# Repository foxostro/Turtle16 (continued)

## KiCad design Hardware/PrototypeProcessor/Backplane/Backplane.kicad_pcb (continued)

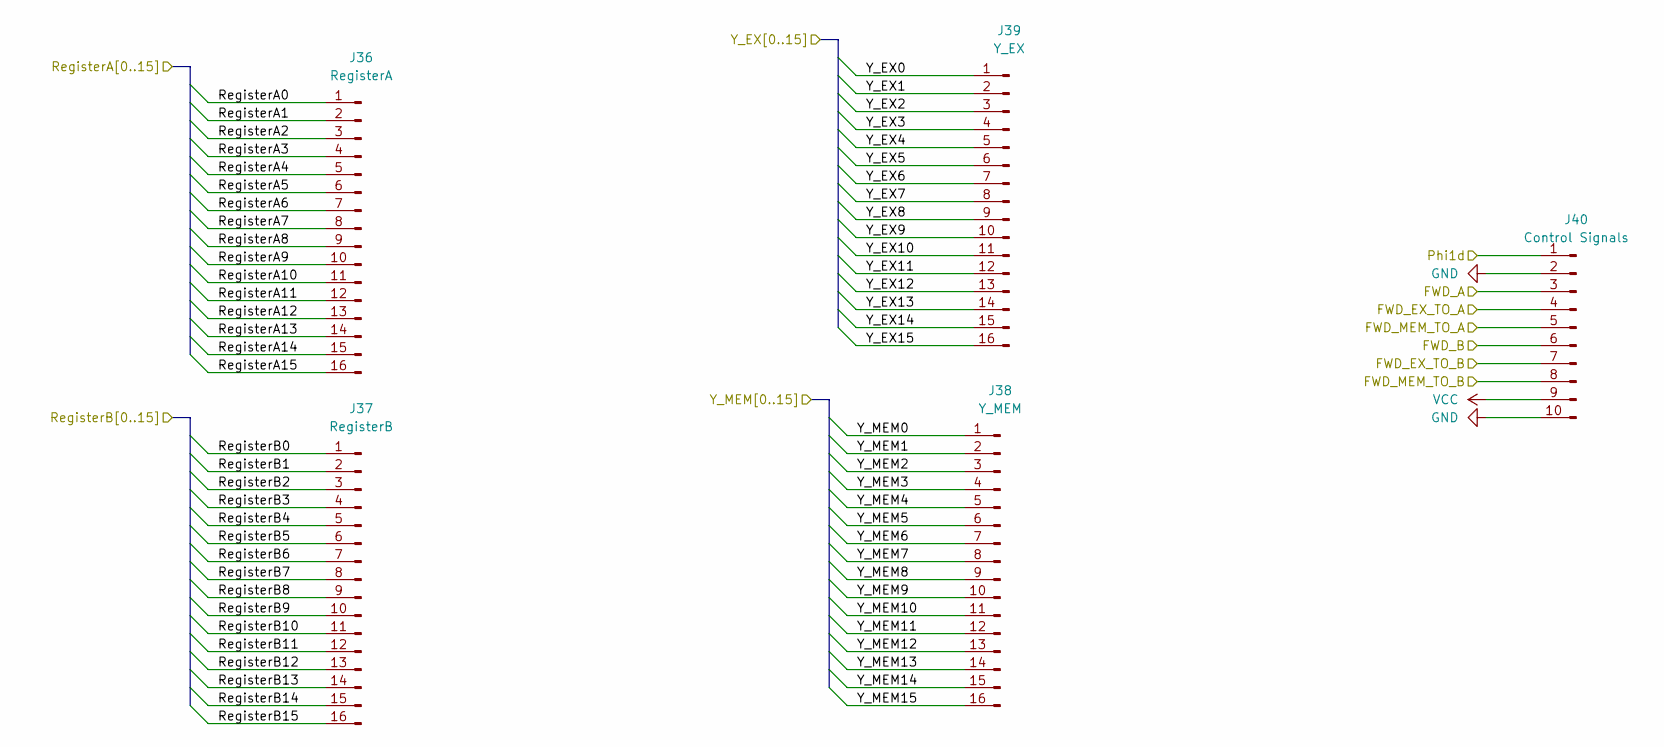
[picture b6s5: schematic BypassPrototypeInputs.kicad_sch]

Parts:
J36: RegisterA; PinHeader_1x16_P2.54mm_Vertical
J37: RegisterB; PinHeader_1x16_P2.54mm_Vertical
J38: Y_MEM; PinHeader_1x16_P2.54mm_Vertical
J39: Y_EX; PinHeader_1x16_P2.54mm_Vertical
J40: Control Signals; PinHeader_1x10_P2.54mm_Vertical

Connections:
/FWD_A: J40.3; also elsewhere on the board
/FWD_B: J40.6; also elsewhere on the board
/FWD_EX_TO_A: J40.4; also elsewhere on the board
/FWD_EX_TO_B: J40.7; also elsewhere on the board
/FWD_MEM_TO_A: J40.5; also elsewhere on the board
/FWD_MEM_TO_B: J40.8; also elsewhere on the board
/Phi1d: J40.1; also elsewhere on the board
/RegisterA0: J36.1; also elsewhere on the board
/RegisterA1: J36.2; also elsewhere on the board
/RegisterA2: J36.3; also elsewhere on the board
/RegisterA3: J36.4; also elsewhere on the board
/RegisterA4: J36.5; also elsewhere on the board
/RegisterA5: J36.6; also elsewhere on the board
/RegisterA6: J36.7; also elsewhere on the board
/RegisterA7: J36.8; also elsewhere on the board
/RegisterA8: J36.9; also elsewhere on the board
/RegisterA9: J36.10; also elsewhere on the board
/RegisterA10: J36.11; also elsewhere on the board
/RegisterA11: J36.12; also elsewhere on the board
/RegisterA12: J36.13; also elsewhere on the board
/RegisterA13: J36.14; also elsewhere on the board
/RegisterA14: J36.15; also elsewhere on the board
/RegisterA15: J36.16; also elsewhere on the board
/RegisterB0: J37.1; also elsewhere on the board
/RegisterB1: J37.2; also elsewhere on the board
/RegisterB2: J37.3; also elsewhere on the board
/RegisterB3: J37.4; also elsewhere on the board
/RegisterB4: J37.5; also elsewhere on the board
/RegisterB5: J37.6; also elsewhere on the board
/RegisterB6: J37.7; also elsewhere on the board
/RegisterB7: J37.8; also elsewhere on the board
/RegisterB8: J37.9; also elsewhere on the board
/RegisterB9: J37.10; also elsewhere on the board
/RegisterB10: J37.11; also elsewhere on the board
/RegisterB11: J37.12; also elsewhere on the board
/RegisterB12: J37.13; also elsewhere on the board
/RegisterB13: J37.14; also elsewhere on the board
/RegisterB14: J37.15; also elsewhere on the board
/RegisterB15: J37.16; also elsewhere on the board
/Y_EX0: J39.1; also elsewhere on the board
/Y_EX1: J39.2; also elsewhere on the board
/Y_EX2: J39.3; also elsewhere on the board
/Y_EX3: J39.4; also elsewhere on the board
/Y_EX4: J39.5; also elsewhere on the board
/Y_EX5: J39.6; also elsewhere on the board
/Y_EX6: J39.7; also elsewhere on the board
/Y_EX7: J39.8; also elsewhere on the board
/Y_EX8: J39.9; also elsewhere on the board
/Y_EX9: J39.10; also elsewhere on the board
/Y_EX10: J39.11; also elsewhere on the board
/Y_EX11: J39.12; also elsewhere on the board
/Y_EX12: J39.13; also elsewhere on the board
/Y_EX13: J39.14; also elsewhere on the board
/Y_EX14: J39.15; also elsewhere on the board
/Y_EX15: J39.16; also elsewhere on the board
/Y_MEM0: J38.1; also elsewhere on the board
/Y_MEM1: J38.2; also elsewhere on the board
/Y_MEM2: J38.3; also elsewhere on the board
/Y_MEM3: J38.4; also elsewhere on the board
/Y_MEM4: J38.5; also elsewhere on the board
/Y_MEM5: J38.6; also elsewhere on the board
/Y_MEM6: J38.7; also elsewhere on the board
/Y_MEM7: J38.8; also elsewhere on the board
/Y_MEM8: J38.9; also elsewhere on the board
/Y_MEM9: J38.10; also elsewhere on the board
/Y_MEM10: J38.11; also elsewhere on the board
/Y_MEM11: J38.12; also elsewhere on the board
/Y_MEM12: J38.13; also elsewhere on the board
/Y_MEM13: J38.14; also elsewhere on the board
/Y_MEM14: J38.15; also elsewhere on the board
/Y_MEM15: J38.16; also elsewhere on the board
GND: J40.2, J40.10; also elsewhere on the board
VCC: J40.9; also elsewhere on the board

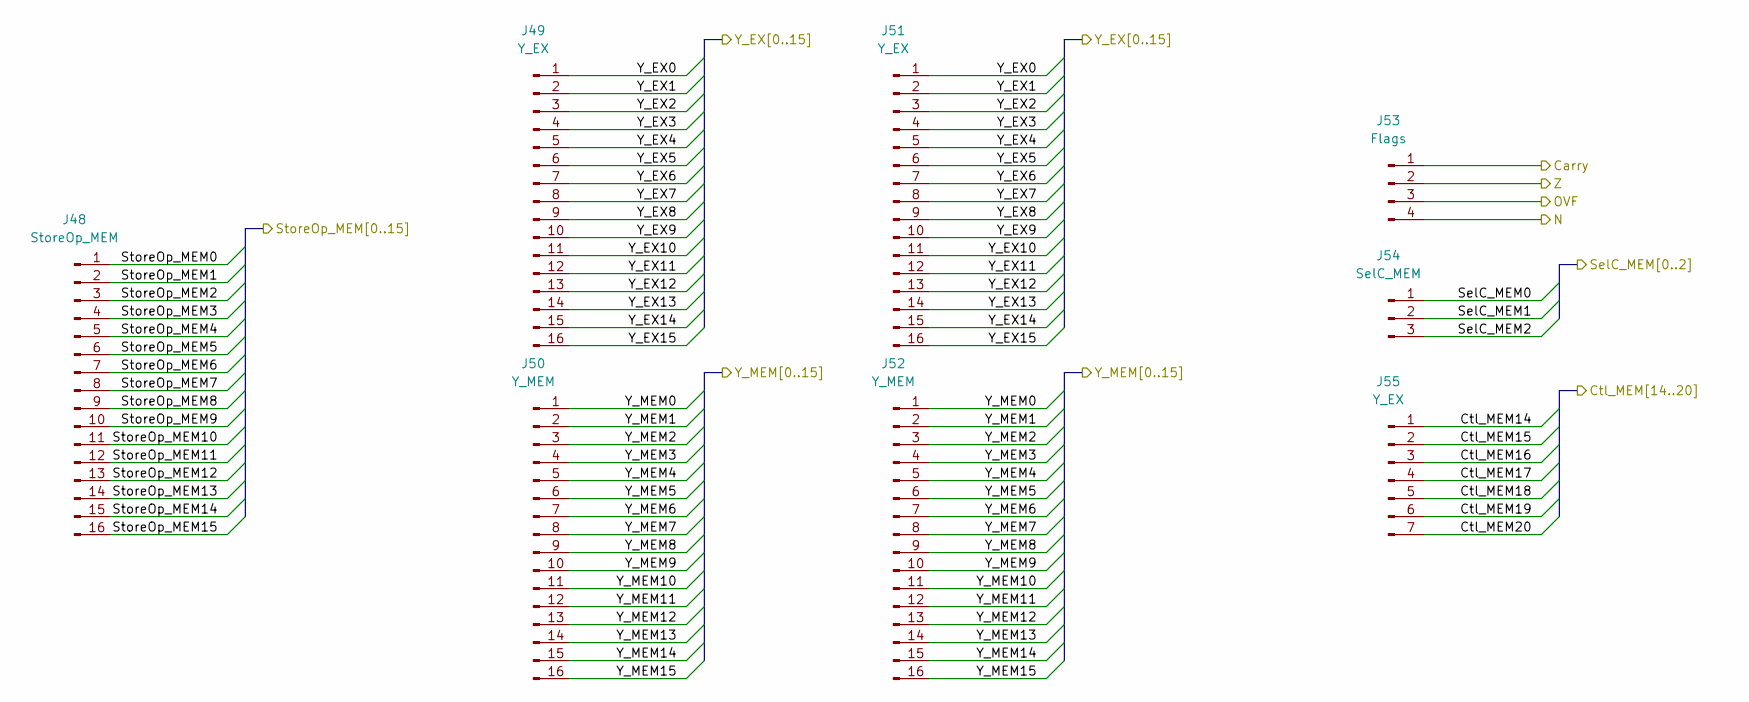
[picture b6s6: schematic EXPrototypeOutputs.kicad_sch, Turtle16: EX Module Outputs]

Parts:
J48: StoreOp_MEM; PinHeader_1x16_P2.54mm_Vertical
J49, J51: Y_EX; PinHeader_1x16_P2.54mm_Vertical
J50, J52: Y_MEM; PinHeader_1x16_P2.54mm_Vertical
J53: Flags; PinHeader_1x04_P2.54mm_Vertical
J54: SelC_MEM; PinHeader_1x03_P2.54mm_Vertical
J55: Y_EX; PinHeader_1x07_P2.54mm_Vertical

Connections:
/Carry: J53.1; also elsewhere on the board
/Ctl_MEM14: J55.1; also elsewhere on the board
/Ctl_MEM15: J55.2; also elsewhere on the board
/Ctl_MEM16: J55.3; also elsewhere on the board
/Ctl_MEM17: J55.4; also elsewhere on the board
/Ctl_MEM18: J55.5; also elsewhere on the board
/Ctl_MEM19: J55.6; also elsewhere on the board
/Ctl_MEM20: J55.7; also elsewhere on the board
/N: J53.4; also elsewhere on the board
/OVF: J53.3; also elsewhere on the board
/SelC_MEM0: J54.1; also elsewhere on the board
/SelC_MEM1: J54.2; also elsewhere on the board
/SelC_MEM2: J54.3; also elsewhere on the board
/StoreOp_MEM0: J48.1; also elsewhere on the board
/StoreOp_MEM1: J48.2; also elsewhere on the board
/StoreOp_MEM2: J48.3; also elsewhere on the board
/StoreOp_MEM3: J48.4; also elsewhere on the board
/StoreOp_MEM4: J48.5; also elsewhere on the board
/StoreOp_MEM5: J48.6; also elsewhere on the board
/StoreOp_MEM6: J48.7; also elsewhere on the board
/StoreOp_MEM7: J48.8; also elsewhere on the board
/StoreOp_MEM8: J48.9; also elsewhere on the board
/StoreOp_MEM9: J48.10; also elsewhere on the board
/StoreOp_MEM10: J48.11; also elsewhere on the board
/StoreOp_MEM11: J48.12; also elsewhere on the board
/StoreOp_MEM12: J48.13; also elsewhere on the board
/StoreOp_MEM13: J48.14; also elsewhere on the board
/StoreOp_MEM14: J48.15; also elsewhere on the board
/StoreOp_MEM15: J48.16; also elsewhere on the board
/Y_EX0: J49.1, J51.1; also elsewhere on the board
/Y_EX1: J49.2, J51.2; also elsewhere on the board
/Y_EX2: J49.3, J51.3; also elsewhere on the board
/Y_EX3: J49.4, J51.4; also elsewhere on the board
/Y_EX4: J49.5, J51.5; also elsewhere on the board
/Y_EX5: J49.6, J51.6; also elsewhere on the board
/Y_EX6: J49.7, J51.7; also elsewhere on the board
/Y_EX7: J49.8, J51.8; also elsewhere on the board
/Y_EX8: J49.9, J51.9; also elsewhere on the board
/Y_EX9: J49.10, J51.10; also elsewhere on the board
/Y_EX10: J49.11, J51.11; also elsewhere on the board
/Y_EX11: J49.12, J51.12; also elsewhere on the board
/Y_EX12: J49.13, J51.13; also elsewhere on the board
/Y_EX13: J49.14, J51.14; also elsewhere on the board
/Y_EX14: J49.15, J51.15; also elsewhere on the board
/Y_EX15: J49.16, J51.16; also elsewhere on the board
/Y_MEM0: J50.1, J52.1; also elsewhere on the board
/Y_MEM1: J50.2, J52.2; also elsewhere on the board
/Y_MEM2: J50.3, J52.3; also elsewhere on the board
/Y_MEM3: J50.4, J52.4; also elsewhere on the board
/Y_MEM4: J50.5, J52.5; also elsewhere on the board
/Y_MEM5: J50.6, J52.6; also elsewhere on the board
/Y_MEM6: J50.7, J52.7; also elsewhere on the board
/Y_MEM7: J50.8, J52.8; also elsewhere on the board
/Y_MEM8: J50.9, J52.9; also elsewhere on the board
/Y_MEM9: J50.10, J52.10; also elsewhere on the board
/Y_MEM10: J50.11, J52.11; also elsewhere on the board
/Y_MEM11: J50.12, J52.12; also elsewhere on the board
/Y_MEM12: J50.13, J52.13; also elsewhere on the board
/Y_MEM13: J50.14, J52.14; also elsewhere on the board
/Y_MEM14: J50.15, J52.15; also elsewhere on the board
/Y_MEM15: J50.16, J52.16; also elsewhere on the board
/Z: J53.2; also elsewhere on the board

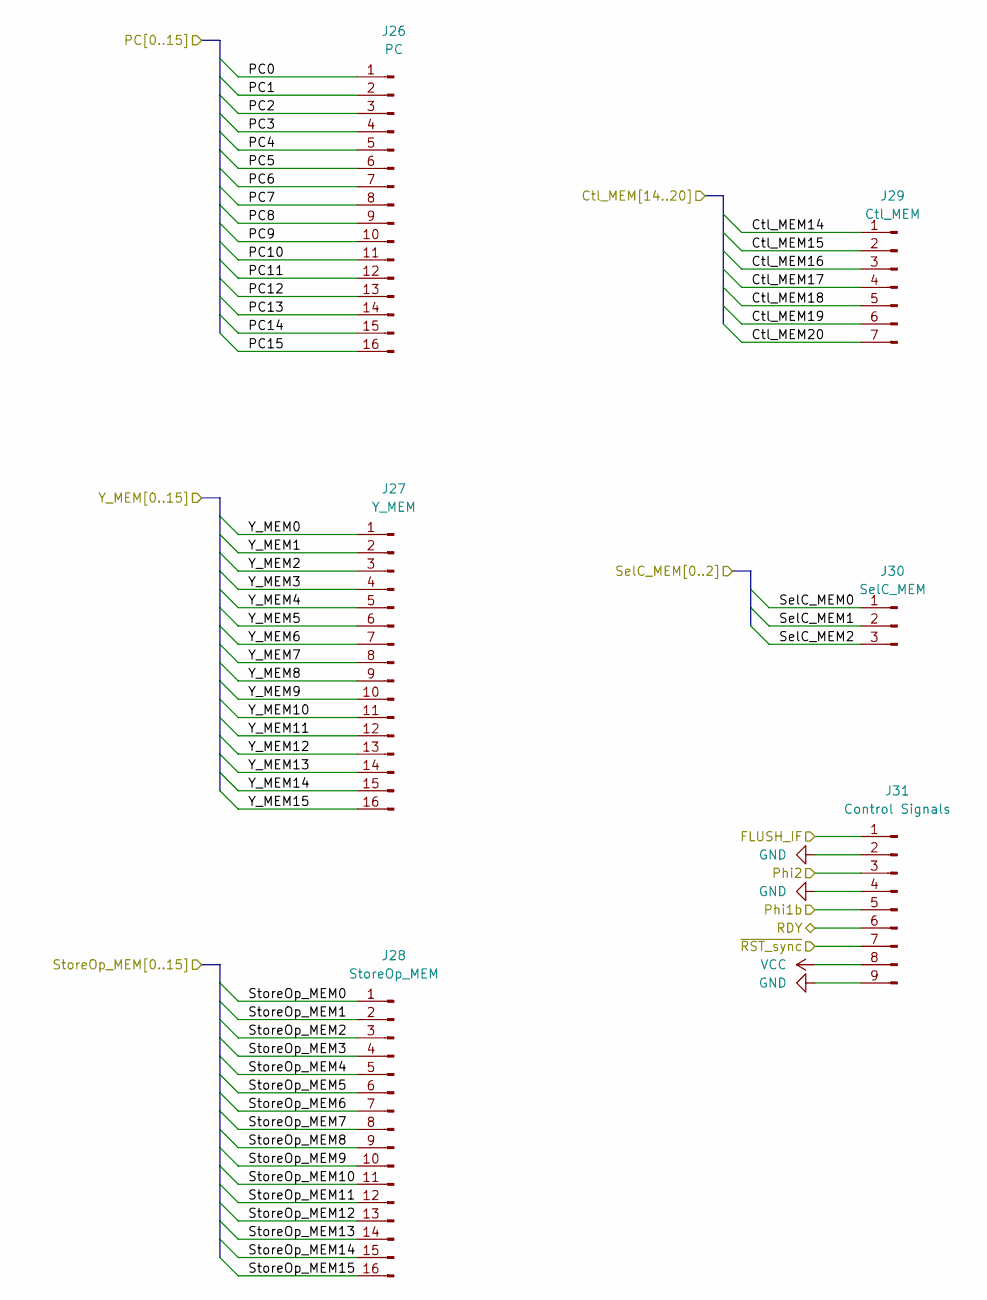
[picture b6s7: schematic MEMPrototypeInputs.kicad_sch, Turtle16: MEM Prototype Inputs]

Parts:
J26: PC; PinHeader_1x16_P2.54mm_Vertical
J27: Y_MEM; PinHeader_1x16_P2.54mm_Vertical
J28: StoreOp_MEM; PinHeader_1x16_P2.54mm_Vertical
J29: Ctl_MEM; PinHeader_1x07_P2.54mm_Vertical
J30: SelC_MEM; PinHeader_1x03_P2.54mm_Vertical
J31: Control Signals; PinHeader_1x09_P2.54mm_Vertical

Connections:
/Ctl_MEM14: J29.1; also elsewhere on the board
/Ctl_MEM15: J29.2; also elsewhere on the board
/Ctl_MEM16: J29.3; also elsewhere on the board
/Ctl_MEM17: J29.4; also elsewhere on the board
/Ctl_MEM18: J29.5; also elsewhere on the board
/Ctl_MEM19: J29.6; also elsewhere on the board
/Ctl_MEM20: J29.7; also elsewhere on the board
/FLUSH_IF: J31.1; also elsewhere on the board
/PC0: J26.1; also elsewhere on the board
/PC1: J26.2; also elsewhere on the board
/PC2: J26.3; also elsewhere on the board
/PC3: J26.4; also elsewhere on the board
/PC4: J26.5; also elsewhere on the board
/PC5: J26.6; also elsewhere on the board
/PC6: J26.7; also elsewhere on the board
/PC7: J26.8; also elsewhere on the board
/PC8: J26.9; also elsewhere on the board
/PC9: J26.10; also elsewhere on the board
/PC10: J26.11; also elsewhere on the board
/PC11: J26.12; also elsewhere on the board
/PC12: J26.13; also elsewhere on the board
/PC13: J26.14; also elsewhere on the board
/PC14: J26.15; also elsewhere on the board
/PC15: J26.16; also elsewhere on the board
/Phi1b: J31.5; also elsewhere on the board
/Phi2: J31.3; also elsewhere on the board
/RDY: J31.6; also elsewhere on the board
/SelC_MEM0: J30.1; also elsewhere on the board
/SelC_MEM1: J30.2; also elsewhere on the board
/SelC_MEM2: J30.3; also elsewhere on the board
/StoreOp_MEM0: J28.1; also elsewhere on the board
/StoreOp_MEM1: J28.2; also elsewhere on the board
/StoreOp_MEM2: J28.3; also elsewhere on the board
/StoreOp_MEM3: J28.4; also elsewhere on the board
/StoreOp_MEM4: J28.5; also elsewhere on the board
/StoreOp_MEM5: J28.6; also elsewhere on the board
/StoreOp_MEM6: J28.7; also elsewhere on the board
/StoreOp_MEM7: J28.8; also elsewhere on the board
/StoreOp_MEM8: J28.9; also elsewhere on the board
/StoreOp_MEM9: J28.10; also elsewhere on the board
/StoreOp_MEM10: J28.11; also elsewhere on the board
/StoreOp_MEM11: J28.12; also elsewhere on the board
/StoreOp_MEM12: J28.13; also elsewhere on the board
/StoreOp_MEM13: J28.14; also elsewhere on the board
/StoreOp_MEM14: J28.15; also elsewhere on the board
/StoreOp_MEM15: J28.16; also elsewhere on the board
/Y_MEM0: J27.1; also elsewhere on the board
/Y_MEM1: J27.2; also elsewhere on the board
/Y_MEM2: J27.3; also elsewhere on the board
/Y_MEM3: J27.4; also elsewhere on the board
/Y_MEM4: J27.5; also elsewhere on the board
/Y_MEM5: J27.6; also elsewhere on the board
/Y_MEM6: J27.7; also elsewhere on the board
/Y_MEM7: J27.8; also elsewhere on the board
/Y_MEM8: J27.9; also elsewhere on the board
/Y_MEM9: J27.10; also elsewhere on the board
/Y_MEM10: J27.11; also elsewhere on the board
/Y_MEM11: J27.12; also elsewhere on the board
/Y_MEM12: J27.13; also elsewhere on the board
/Y_MEM13: J27.14; also elsewhere on the board
/Y_MEM14: J27.15; also elsewhere on the board
/Y_MEM15: J27.16; also elsewhere on the board
/~RST_sync: J31.7; also elsewhere on the board
GND: J31.2, J31.4, J31.9; also elsewhere on the board
VCC: J31.8; also elsewhere on the board

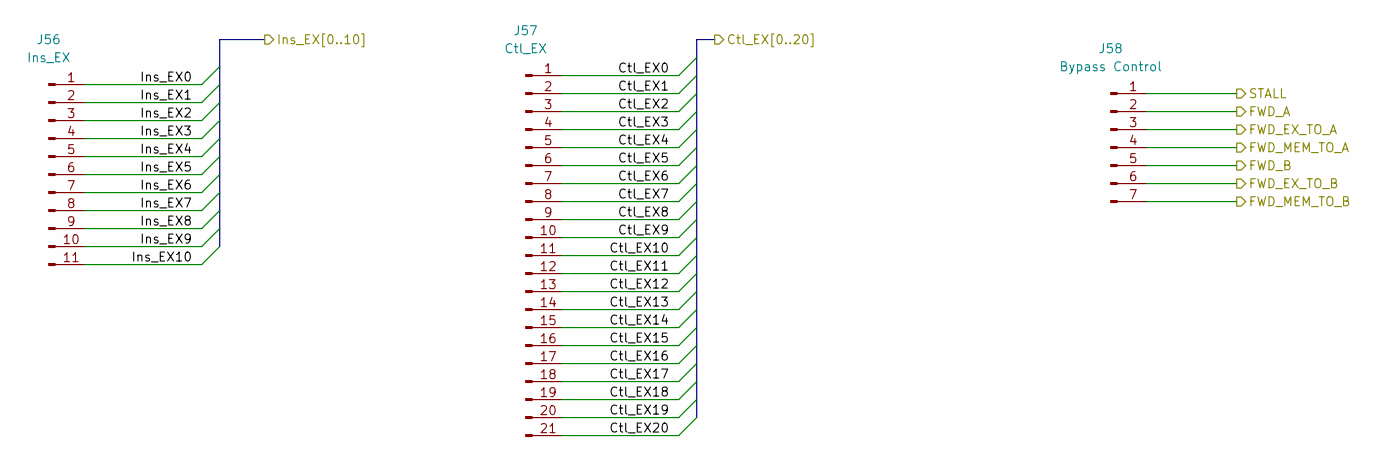
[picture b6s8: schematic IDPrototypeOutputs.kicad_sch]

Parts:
J56: Ins_EX; PinHeader_1x11_P2.54mm_Vertical
J57: Ctl_EX; PinHeader_1x21_P2.54mm_Vertical
J58: Bypass Control; PinHeader_1x07_P2.54mm_Vertical

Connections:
/Ctl_EX0: J57.1; also elsewhere on the board
/Ctl_EX1: J57.2; also elsewhere on the board
/Ctl_EX2: J57.3; also elsewhere on the board
/Ctl_EX3: J57.4; also elsewhere on the board
/Ctl_EX4: J57.5; also elsewhere on the board
/Ctl_EX5: J57.6; also elsewhere on the board
/Ctl_EX6: J57.7; also elsewhere on the board
/Ctl_EX7: J57.8; also elsewhere on the board
/Ctl_EX8: J57.9; also elsewhere on the board
/Ctl_EX9: J57.10; also elsewhere on the board
/Ctl_EX10: J57.11; also elsewhere on the board
/Ctl_EX11: J57.12; also elsewhere on the board
/Ctl_EX12: J57.13; also elsewhere on the board
/Ctl_EX13: J57.14; also elsewhere on the board
/Ctl_EX14: J57.15; also elsewhere on the board
/Ctl_EX15: J57.16; also elsewhere on the board
/Ctl_EX16: J57.17; also elsewhere on the board
/Ctl_EX17: J57.18; also elsewhere on the board
/Ctl_EX18: J57.19; also elsewhere on the board
/Ctl_EX19: J57.20; also elsewhere on the board
/Ctl_EX20: J57.21; also elsewhere on the board
/FWD_A: J58.2; also elsewhere on the board
/FWD_B: J58.5; also elsewhere on the board
/FWD_EX_TO_A: J58.3; also elsewhere on the board
/FWD_EX_TO_B: J58.6; also elsewhere on the board
/FWD_MEM_TO_A: J58.4; also elsewhere on the board
/FWD_MEM_TO_B: J58.7; also elsewhere on the board
/Ins_EX0: J56.1; also elsewhere on the board
/Ins_EX1: J56.2; also elsewhere on the board
/Ins_EX2: J56.3; also elsewhere on the board
/Ins_EX3: J56.4; also elsewhere on the board
/Ins_EX4: J56.5; also elsewhere on the board
/Ins_EX5: J56.6; also elsewhere on the board
/Ins_EX6: J56.7; also elsewhere on the board
/Ins_EX7: J56.8; also elsewhere on the board
/Ins_EX8: J56.9; also elsewhere on the board
/Ins_EX9: J56.10; also elsewhere on the board
/Ins_EX10: J56.11; also elsewhere on the board
/STALL: J58.1; also elsewhere on the board

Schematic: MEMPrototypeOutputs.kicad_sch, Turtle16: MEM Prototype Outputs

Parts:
J43: StoreOp_WB; PinHeader_1x16_P2.54mm_Vertical
J44: Ins_IF; PinHeader_1x16_P2.54mm_Vertical
J45: SelC_MEM; PinHeader_1x03_P2.54mm_Vertical
J46: Y_WB; PinHeader_1x16_P2.54mm_Vertical
J47: Ctl_MEM; PinHeader_1x04_P2.54mm_Vertical

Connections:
/Ctl_WB17: J47.1; also elsewhere on the board
/Ctl_WB18: J47.2; also elsewhere on the board
/Ctl_WB19: J47.3; also elsewhere on the board
/Ctl_WB20: J47.4; also elsewhere on the board
/Ins_IF0: J44.1; also elsewhere on the board
/Ins_IF1: J44.2; also elsewhere on the board
/Ins_IF2: J44.3; also elsewhere on the board
/Ins_IF3: J44.4; also elsewhere on the board
/Ins_IF4: J44.5; also elsewhere on the board
/Ins_IF5: J44.6; also elsewhere on the board
/Ins_IF6: J44.7; also elsewhere on the board
/Ins_IF7: J44.8; also elsewhere on the board
/Ins_IF8: J44.9; also elsewhere on the board
/Ins_IF9: J44.10; also elsewhere on the board
/Ins_IF10: J44.11; also elsewhere on the board
/Ins_IF11: J44.12; also elsewhere on the board
/Ins_IF12: J44.13; also elsewhere on the board
/Ins_IF13: J44.14; also elsewhere on the board
/Ins_IF14: J44.15; also elsewhere on the board
/Ins_IF15: J44.16; also elsewhere on the board
/SelC_WB0: J45.1; also elsewhere on the board
/SelC_WB1: J45.2; also elsewhere on the board
/SelC_WB2: J45.3; also elsewhere on the board
/StoreOp_WB0: J43.1; also elsewhere on the board
/StoreOp_WB1: J43.2; also elsewhere on the board
/StoreOp_WB2: J43.3; also elsewhere on the board
/StoreOp_WB3: J43.4; also elsewhere on the board
/StoreOp_WB4: J43.5; also elsewhere on the board
/StoreOp_WB5: J43.6; also elsewhere on the board
/StoreOp_WB6: J43.7; also elsewhere on the board
/StoreOp_WB7: J43.8; also elsewhere on the board
/StoreOp_WB8: J43.9; also elsewhere on the board
/StoreOp_WB9: J43.10; also elsewhere on the board
/StoreOp_WB10: J43.11; also elsewhere on the board
/StoreOp_WB11: J43.12; also elsewhere on the board
/StoreOp_WB12: J43.13; also elsewhere on the board
/StoreOp_WB13: J43.14; also elsewhere on the board
/StoreOp_WB14: J43.15; also elsewhere on the board
/StoreOp_WB15: J43.16; also elsewhere on the board
/Y_WB0: J46.1; also elsewhere on the board
/Y_WB1: J46.2; also elsewhere on the board
/Y_WB2: J46.3; also elsewhere on the board
/Y_WB3: J46.4; also elsewhere on the board
/Y_WB4: J46.5; also elsewhere on the board
/Y_WB5: J46.6; also elsewhere on the board
/Y_WB6: J46.7; also elsewhere on the board
/Y_WB7: J46.8; also elsewhere on the board
/Y_WB8: J46.9; also elsewhere on the board
/Y_WB9: J46.10; also elsewhere on the board
/Y_WB10: J46.11; also elsewhere on the board
/Y_WB11: J46.12; also elsewhere on the board
/Y_WB12: J46.13; also elsewhere on the board
/Y_WB13: J46.14; also elsewhere on the board
/Y_WB14: J46.15; also elsewhere on the board
/Y_WB15: J46.16; also elsewhere on the board

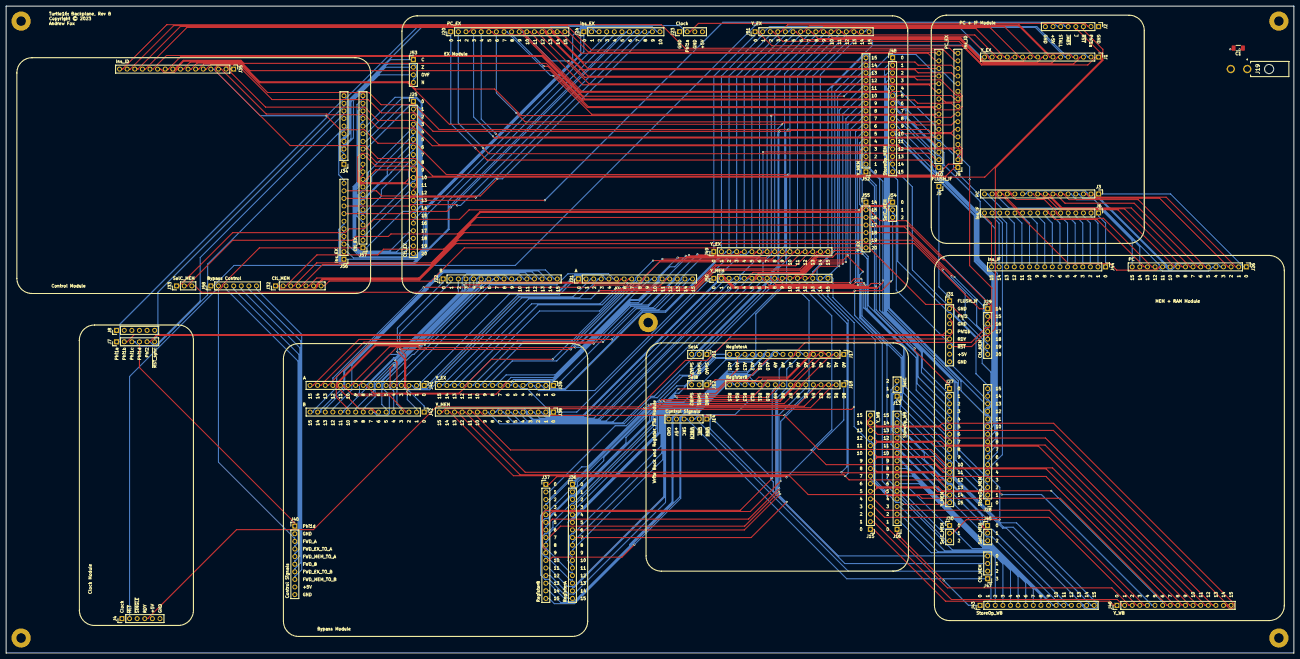
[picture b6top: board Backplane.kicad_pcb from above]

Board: 4 copper layers, 430.0 x 216.0 mm, 64 parts (0 on the bottom side), 278 nets.

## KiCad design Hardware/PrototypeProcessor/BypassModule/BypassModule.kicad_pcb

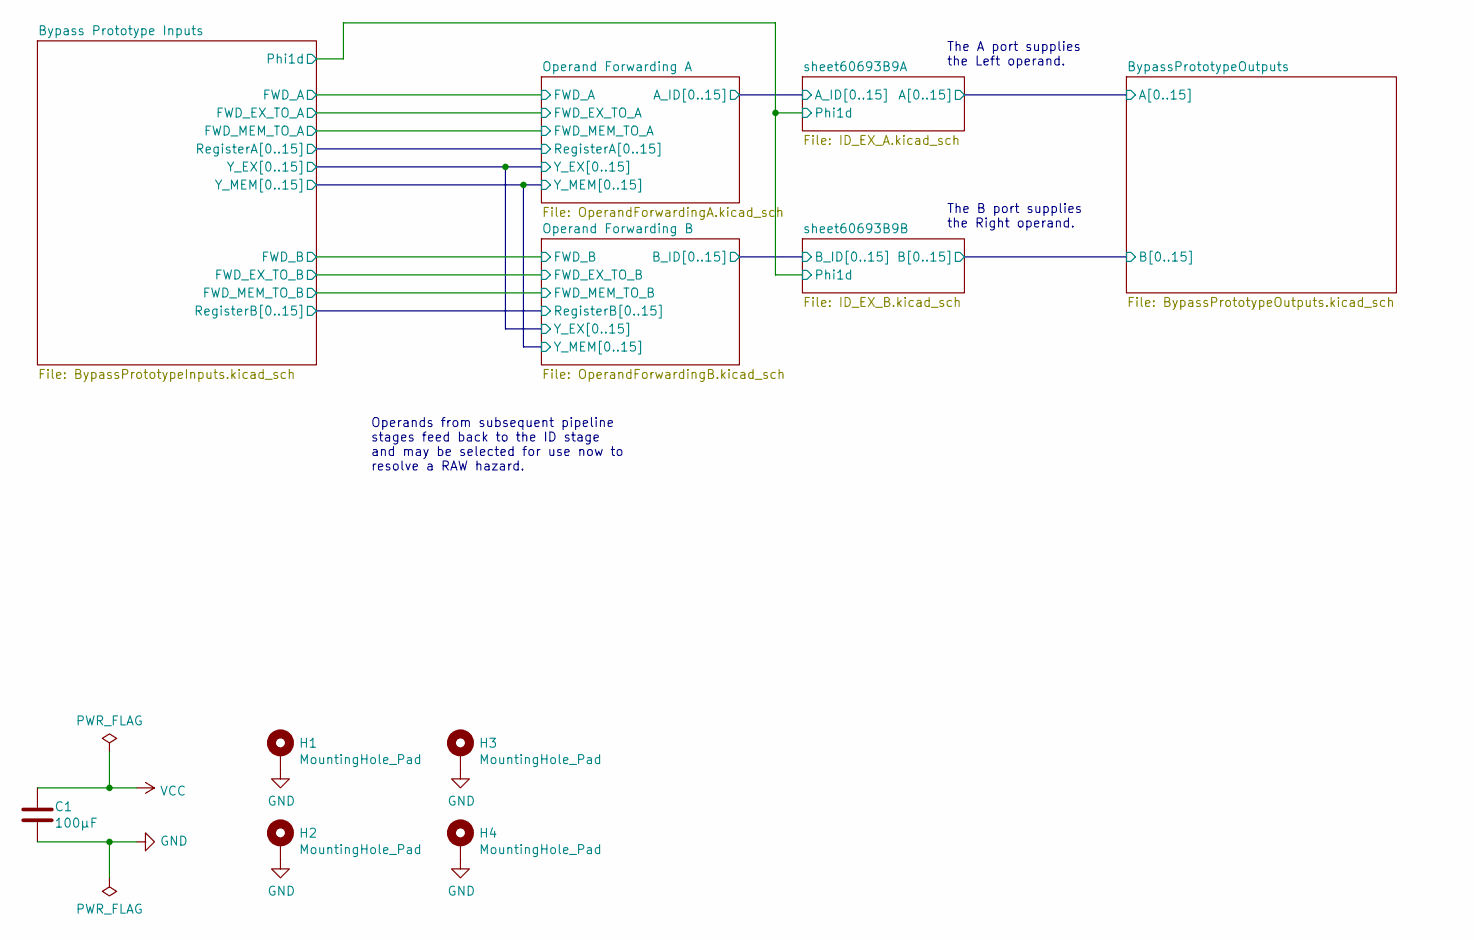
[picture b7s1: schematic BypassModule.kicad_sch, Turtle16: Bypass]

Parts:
C1: 100µF; C_1206_3216Metric_Pad1.33x1.80mm_HandSolder
H1, H2, H3, H4: MountingHole_Pad; MountingHole_3.2mm_M3_Pad

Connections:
GND: C1.2, H1.1, H2.1, H3.1, H4.1; also elsewhere on the board
VCC: C1.1; also elsewhere on the board

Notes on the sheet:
Operands from subsequent pipeline stages feed back to the ID stage and may be selected for use now to resolve a RAW hazard.
The B port supplies the Right operand.
The A port supplies the Left operand.

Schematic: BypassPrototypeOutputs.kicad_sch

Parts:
J6: A; PinHeader_1x16_P2.54mm_Vertical
J7: B; PinHeader_1x16_P2.54mm_Vertical

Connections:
/BypassPrototypeOutputs/A0: J6.1; also elsewhere on the board
/BypassPrototypeOutputs/A1: J6.2; also elsewhere on the board
/BypassPrototypeOutputs/A2: J6.3; also elsewhere on the board
/BypassPrototypeOutputs/A3: J6.4; also elsewhere on the board
/BypassPrototypeOutputs/A4: J6.5; also elsewhere on the board
/BypassPrototypeOutputs/A5: J6.6; also elsewhere on the board
/BypassPrototypeOutputs/A6: J6.7; also elsewhere on the board
/BypassPrototypeOutputs/A7: J6.8; also elsewhere on the board
/BypassPrototypeOutputs/A8: J6.9; also elsewhere on the board
/BypassPrototypeOutputs/A9: J6.10; also elsewhere on the board
/BypassPrototypeOutputs/A10: J6.11; also elsewhere on the board
/BypassPrototypeOutputs/A11: J6.12; also elsewhere on the board
/BypassPrototypeOutputs/A12: J6.13; also elsewhere on the board
/BypassPrototypeOutputs/A13: J6.14; also elsewhere on the board
/BypassPrototypeOutputs/A14: J6.15; also elsewhere on the board
/BypassPrototypeOutputs/A15: J6.16; also elsewhere on the board
/BypassPrototypeOutputs/B0: J7.1; also elsewhere on the board
/BypassPrototypeOutputs/B1: J7.2; also elsewhere on the board
/BypassPrototypeOutputs/B2: J7.3; also elsewhere on the board
/BypassPrototypeOutputs/B3: J7.4; also elsewhere on the board
/BypassPrototypeOutputs/B4: J7.5; also elsewhere on the board
/BypassPrototypeOutputs/B5: J7.6; also elsewhere on the board
/BypassPrototypeOutputs/B6: J7.7; also elsewhere on the board
/BypassPrototypeOutputs/B7: J7.8; also elsewhere on the board
/BypassPrototypeOutputs/B8: J7.9; also elsewhere on the board
/BypassPrototypeOutputs/B9: J7.10; also elsewhere on the board
/BypassPrototypeOutputs/B10: J7.11; also elsewhere on the board
/BypassPrototypeOutputs/B11: J7.12; also elsewhere on the board
/BypassPrototypeOutputs/B12: J7.13; also elsewhere on the board
/BypassPrototypeOutputs/B13: J7.14; also elsewhere on the board
/BypassPrototypeOutputs/B14: J7.15; also elsewhere on the board
/BypassPrototypeOutputs/B15: J7.16; also elsewhere on the board

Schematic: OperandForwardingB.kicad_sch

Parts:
C5, C6, C7: 100nF; C_0603_1608Metric_Pad1.08x0.95mm_HandSolder
U4, U5, U6: 74AHCT16245; TSSOP-48_6.1x12.5mm_P0.5mm

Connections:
/Bypass Prototype Inputs/FWD_B: U4.25 (2~OE), U4.48 (1~OE); also elsewhere on the board
/Bypass Prototype Inputs/FWD_EX_TO_B: U5.25 (2~OE), U5.48 (1~OE); also elsewhere on the board
/Bypass Prototype Inputs/FWD_MEM_TO_B: U6.25 (2~OE), U6.48 (1~OE); also elsewhere on the board
/Bypass Prototype Inputs/RegisterB0: U4.47 (1A1); also elsewhere on the board
/Bypass Prototype Inputs/RegisterB1: U4.46 (1A2); also elsewhere on the board
/Bypass Prototype Inputs/RegisterB2: U4.44 (1A3); also elsewhere on the board
/Bypass Prototype Inputs/RegisterB3: U4.43 (1A4); also elsewhere on the board
/Bypass Prototype Inputs/RegisterB4: U4.41 (1A5); also elsewhere on the board
/Bypass Prototype Inputs/RegisterB5: U4.40 (1A6); also elsewhere on the board
/Bypass Prototype Inputs/RegisterB6: U4.38 (1A7); also elsewhere on the board
/Bypass Prototype Inputs/RegisterB7: U4.37 (1A8); also elsewhere on the board
/Bypass Prototype Inputs/RegisterB8: U4.36 (2A1); also elsewhere on the board
/Bypass Prototype Inputs/RegisterB9: U4.35 (2A2); also elsewhere on the board
/Bypass Prototype Inputs/RegisterB10: U4.33 (2A3); also elsewhere on the board
/Bypass Prototype Inputs/RegisterB11: U4.32 (2A4); also elsewhere on the board
/Bypass Prototype Inputs/RegisterB12: U4.30 (2A5); also elsewhere on the board
/Bypass Prototype Inputs/RegisterB13: U4.29 (2A6); also elsewhere on the board
/Bypass Prototype Inputs/RegisterB14: U4.27 (2A7); also elsewhere on the board
/Bypass Prototype Inputs/RegisterB15: U4.26 (2A8); also elsewhere on the board
/Bypass Prototype Inputs/Y_EX0: U5.47 (1A1); also elsewhere on the board
/Bypass Prototype Inputs/Y_EX1: U5.46 (1A2); also elsewhere on the board
/Bypass Prototype Inputs/Y_EX2: U5.44 (1A3); also elsewhere on the board
/Bypass Prototype Inputs/Y_EX3: U5.43 (1A4); also elsewhere on the board
/Bypass Prototype Inputs/Y_EX4: U5.41 (1A5); also elsewhere on the board
/Bypass Prototype Inputs/Y_EX5: U5.40 (1A6); also elsewhere on the board
/Bypass Prototype Inputs/Y_EX6: U5.38 (1A7); also elsewhere on the board
/Bypass Prototype Inputs/Y_EX7: U5.37 (1A8); also elsewhere on the board
/Bypass Prototype Inputs/Y_EX8: U5.36 (2A1); also elsewhere on the board
/Bypass Prototype Inputs/Y_EX9: U5.35 (2A2); also elsewhere on the board
/Bypass Prototype Inputs/Y_EX10: U5.33 (2A3); also elsewhere on the board
/Bypass Prototype Inputs/Y_EX11: U5.32 (2A4); also elsewhere on the board
/Bypass Prototype Inputs/Y_EX12: U5.30 (2A5); also elsewhere on the board
/Bypass Prototype Inputs/Y_EX13: U5.29 (2A6); also elsewhere on the board
/Bypass Prototype Inputs/Y_EX14: U5.27 (2A7); also elsewhere on the board
/Bypass Prototype Inputs/Y_EX15: U5.26 (2A8); also elsewhere on the board
/Bypass Prototype Inputs/Y_MEM0: U6.47 (1A1); also elsewhere on the board
/Bypass Prototype Inputs/Y_MEM1: U6.46 (1A2); also elsewhere on the board
/Bypass Prototype Inputs/Y_MEM2: U6.44 (1A3); also elsewhere on the board
/Bypass Prototype Inputs/Y_MEM3: U6.43 (1A4); also elsewhere on the board
/Bypass Prototype Inputs/Y_MEM4: U6.41 (1A5); also elsewhere on the board
/Bypass Prototype Inputs/Y_MEM5: U6.40 (1A6); also elsewhere on the board
/Bypass Prototype Inputs/Y_MEM6: U6.38 (1A7); also elsewhere on the board
/Bypass Prototype Inputs/Y_MEM7: U6.37 (1A8); also elsewhere on the board
/Bypass Prototype Inputs/Y_MEM8: U6.36 (2A1); also elsewhere on the board
/Bypass Prototype Inputs/Y_MEM9: U6.35 (2A2); also elsewhere on the board
/Bypass Prototype Inputs/Y_MEM10: U6.33 (2A3); also elsewhere on the board
/Bypass Prototype Inputs/Y_MEM11: U6.32 (2A4); also elsewhere on the board
/Bypass Prototype Inputs/Y_MEM12: U6.30 (2A5); also elsewhere on the board
/Bypass Prototype Inputs/Y_MEM13: U6.29 (2A6); also elsewhere on the board
/Bypass Prototype Inputs/Y_MEM14: U6.27 (2A7); also elsewhere on the board
/Bypass Prototype Inputs/Y_MEM15: U6.26 (2A8); also elsewhere on the board
/Operand Forwarding B/B_ID0: U4.2 (1B1), U5.2 (1B1), U6.2 (1B1); also elsewhere on the board
/Operand Forwarding B/B_ID1: U4.3 (1B2), U5.3 (1B2), U6.3 (1B2); also elsewhere on the board
/Operand Forwarding B/B_ID2: U4.5 (1B3), U5.5 (1B3), U6.5 (1B3); also elsewhere on the board
/Operand Forwarding B/B_ID3: U4.6 (1B4), U5.6 (1B4), U6.6 (1B4); also elsewhere on the board
/Operand Forwarding B/B_ID4: U4.8 (1B5), U5.8 (1B5), U6.8 (1B5); also elsewhere on the board
/Operand Forwarding B/B_ID5: U4.9 (1B6), U5.9 (1B6), U6.9 (1B6); also elsewhere on the board
/Operand Forwarding B/B_ID6: U4.11 (1B7), U5.11 (1B7), U6.11 (1B7); also elsewhere on the board
/Operand Forwarding B/B_ID7: U4.12 (1B8), U5.12 (1B8), U6.12 (1B8); also elsewhere on the board
/Operand Forwarding B/B_ID8: U4.13 (2B1), U5.13 (2B1), U6.13 (2B1); also elsewhere on the board
/Operand Forwarding B/B_ID9: U4.14 (2B2), U5.14 (2B2), U6.14 (2B2); also elsewhere on the board
/Operand Forwarding B/B_ID10: U4.16 (2B3), U5.16 (2B3), U6.16 (2B3); also elsewhere on the board
/Operand Forwarding B/B_ID11: U4.17 (2B4), U5.17 (2B4), U6.17 (2B4); also elsewhere on the board
/Operand Forwarding B/B_ID12: U4.19 (2B5), U5.19 (2B5), U6.19 (2B5); also elsewhere on the board
/Operand Forwarding B/B_ID13: U4.20 (2B6), U5.20 (2B6), U6.20 (2B6); also elsewhere on the board
/Operand Forwarding B/B_ID14: U4.22 (2B7), U5.22 (2B7), U6.22 (2B7); also elsewhere on the board
/Operand Forwarding B/B_ID15: U4.23 (2B8), U5.23 (2B8), U6.23 (2B8); also elsewhere on the board
GND: C5.2, C6.2, C7.2, U4.4 (GND), U4.10 (GND), U4.15 (GND), U4.21 (GND), U4.28 (GND), U4.34 (GND), U4.39 (GND), U4.45 (GND), U5.4 (GND), U5.10 (GND), U5.15 (GND), U5.21 (GND), U5.28 (GND), U5.34 (GND), U5.39 (GND), U5.45 (GND), U6.4 (GND), U6.10 (GND), U6.15 (GND), U6.21 (GND), U6.28 (GND), U6.34 (GND), U6.39 (GND), U6.45 (GND); also elsewhere on the board
VCC: C5.1, C6.1, C7.1, U4.1 (1DIR), U4.7 (VCC), U4.18 (VCC), U4.24 (2DIR), U4.31 (VCC), U4.42 (VCC), U5.1 (1DIR), U5.7 (VCC), U5.18 (VCC), U5.24 (2DIR), U5.31 (VCC), U5.42 (VCC), U6.1 (1DIR), U6.7 (VCC), U6.18 (VCC), U6.24 (2DIR), U6.31 (VCC), U6.42 (VCC); also elsewhere on the board
